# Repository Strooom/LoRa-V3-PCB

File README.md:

# LoRa-V3 PCB

KiCAD design files for the LoRa-V3-PCB.

## Renders
## Front

## Back

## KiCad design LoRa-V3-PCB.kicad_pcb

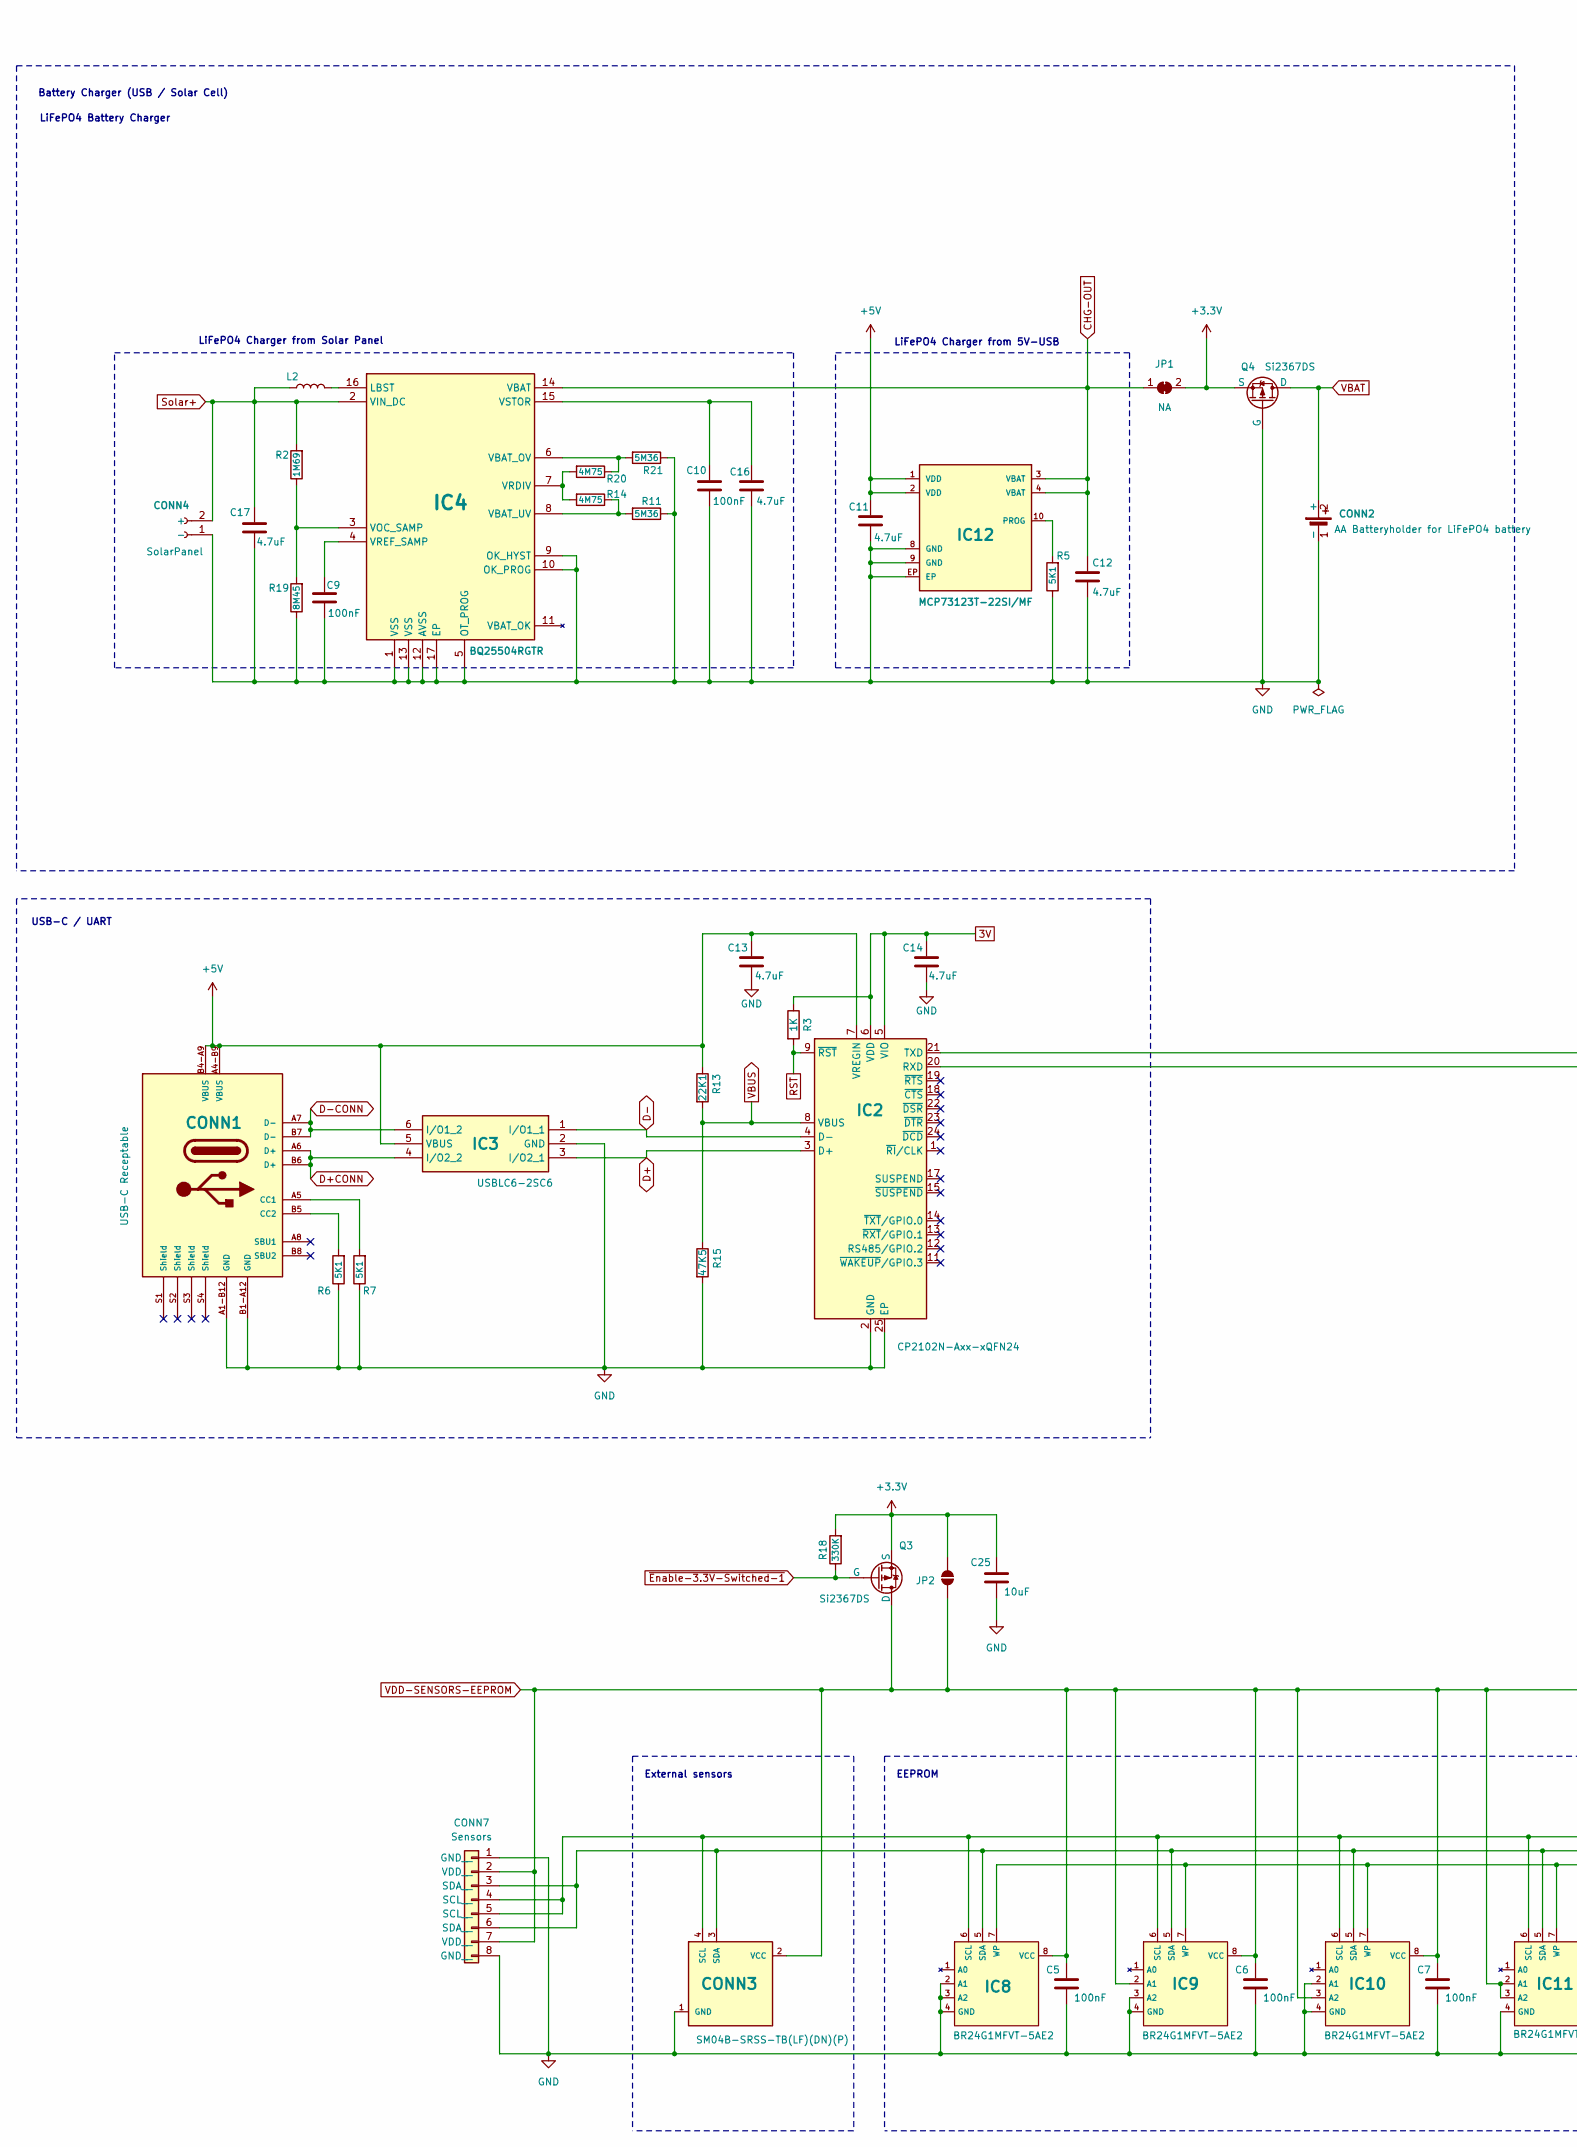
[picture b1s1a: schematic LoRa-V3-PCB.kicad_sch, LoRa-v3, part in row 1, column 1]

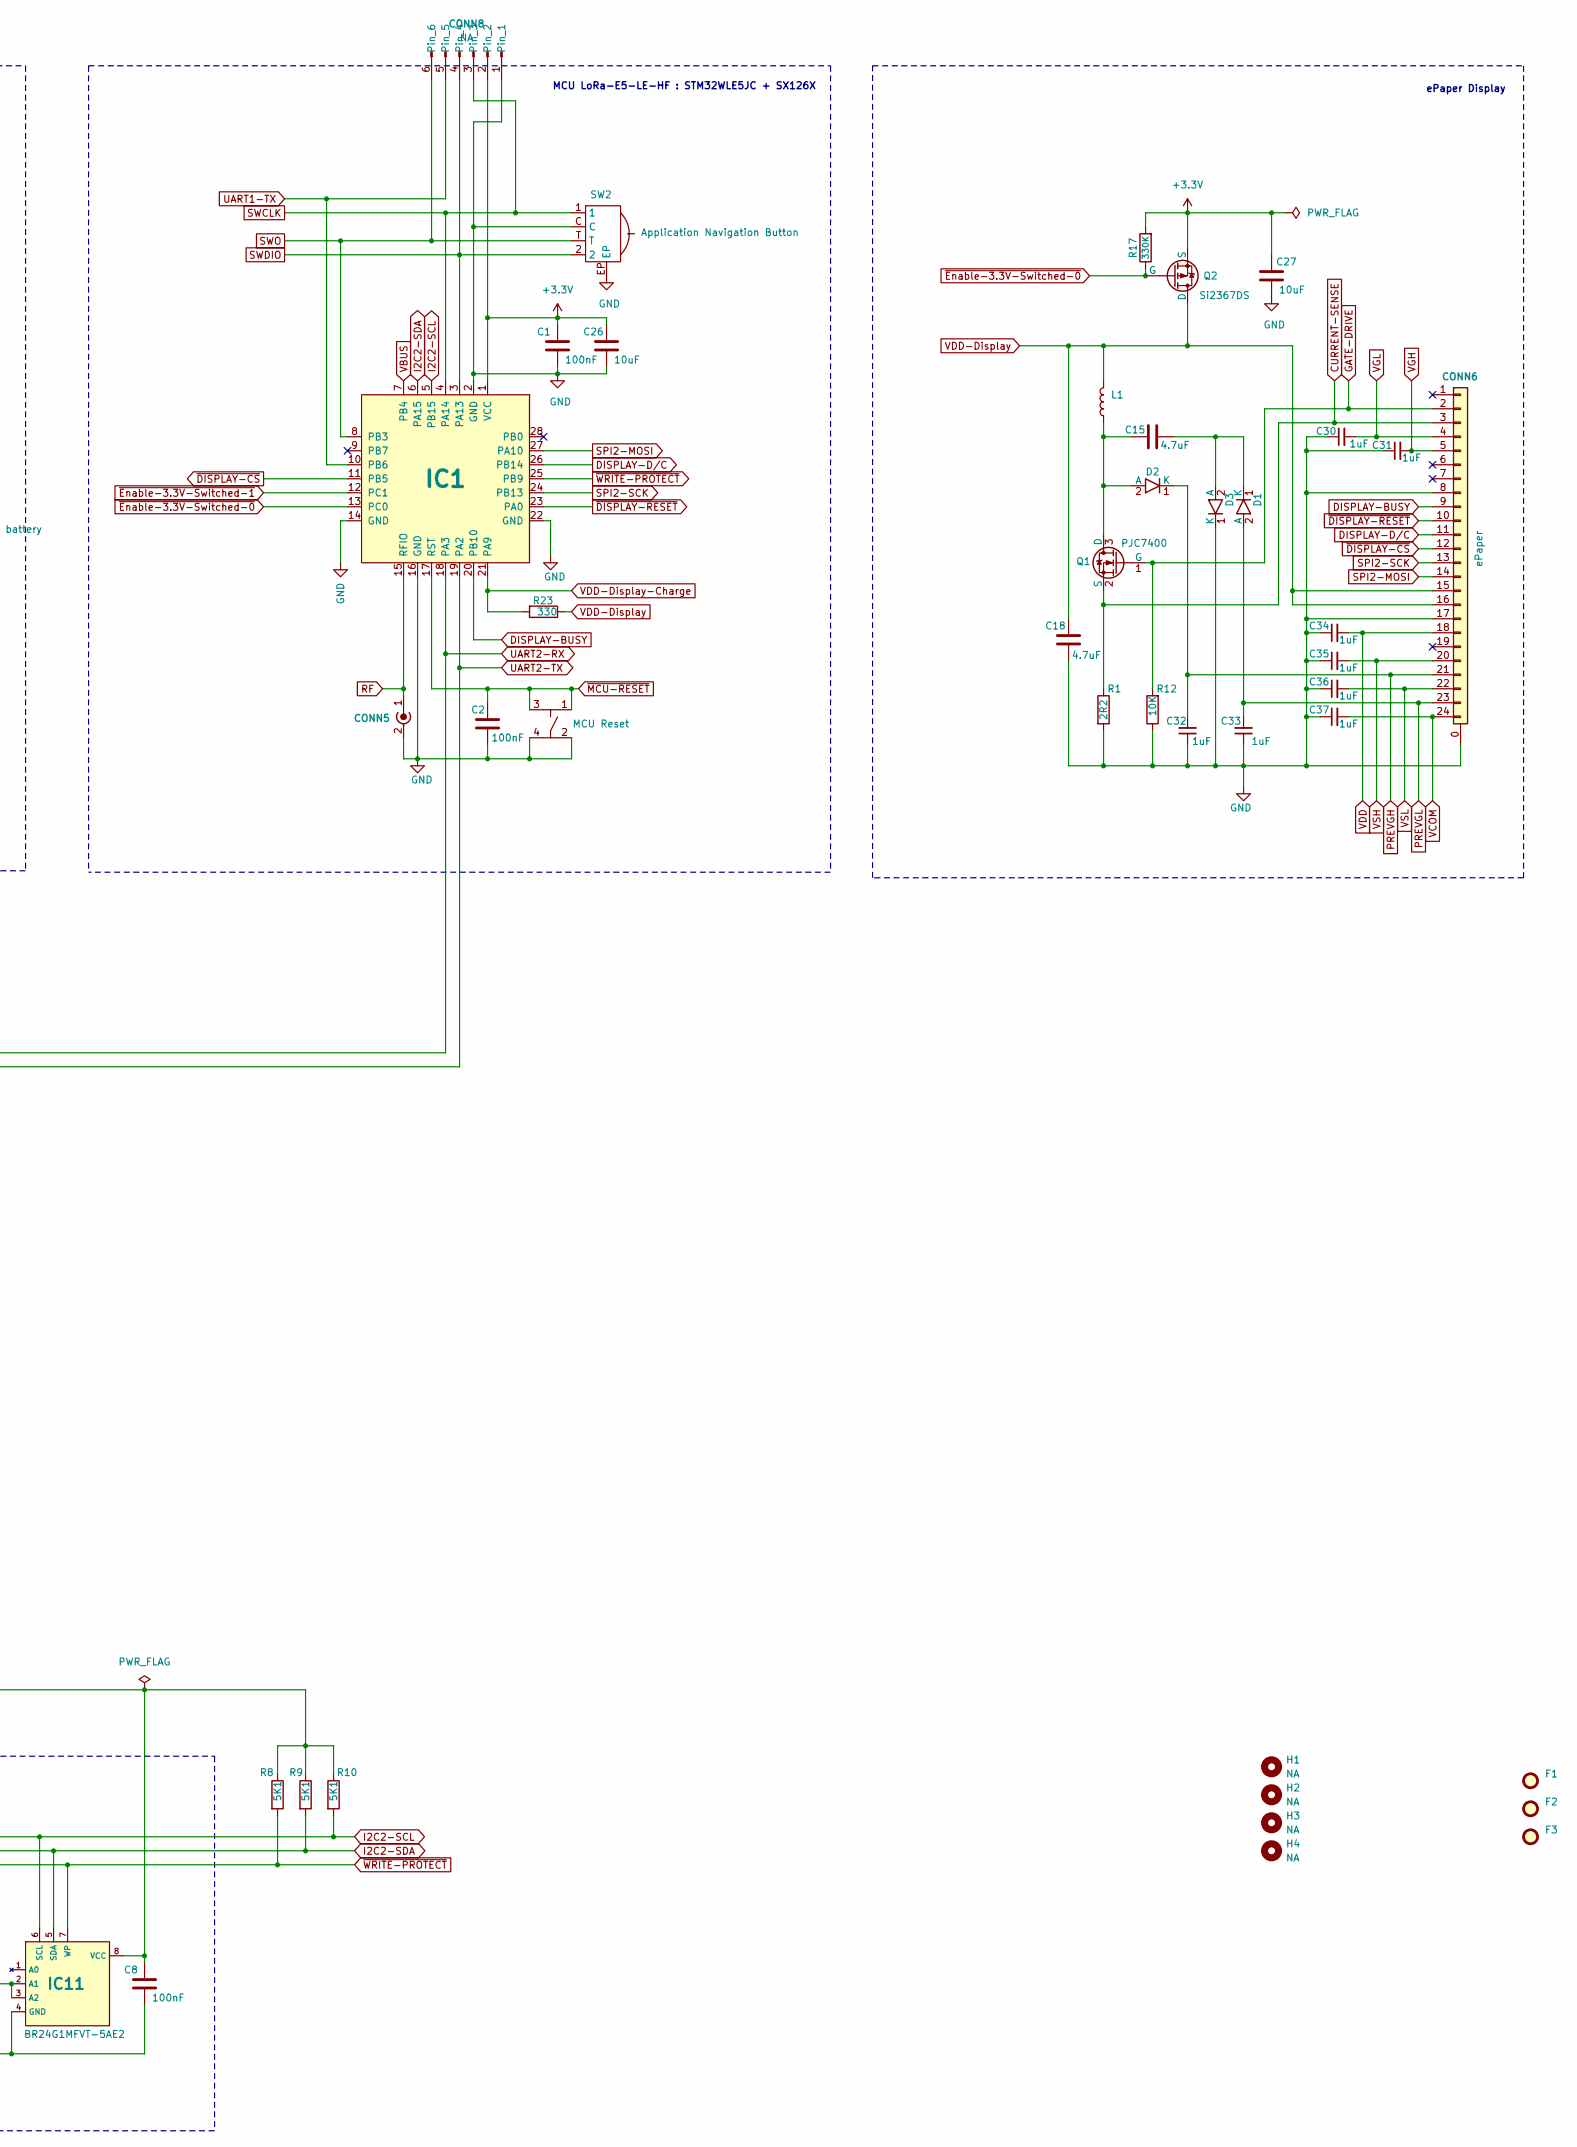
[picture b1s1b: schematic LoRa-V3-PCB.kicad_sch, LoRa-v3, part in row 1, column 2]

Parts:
C1, C2, C5, C6, C7, C8, C9, C10: 100nF; C_0603_nominal; manufacturerPartNumber CGA3E2X7R1E104K080AA
C11, C12, C13, C14, C15, C16, C17, C18: 4.7uF; C_0805; manufacturerPartNumber CL21B475KPFNFNE
C25, C26, C27: 10uF; C_0805; manufacturerPartNumber CL21B106KPQNNWE
C30, C31, C32, C33, C34, C35, C36, C37: 1uF; C_0603_nominal; manufacturerPartNumber CGA3E1X7R1E105K080AC
CONN1: 217179-0001; Molex-2171790001; manufacturerPartNumber 217179-0001
CONN2: AA Batteryholder for LiFePO4 battery; BAT_2460; manufacturerPartNumber 2460
CONN3: SM04B-SRSS-TB(LF)(DN)(P); JST_SH_SM04B-SRSS-TB_1x04-1MP_P1.00mm_Horizontal; manufacturerPartNumber SM04B-SRSS-TB(LF)(DN)(P)
CONN4: NA; PinHeader_1x02_P2.54mm_Vertical; manufacturerPartNumber B2B-XH-A(LF)(SN)
CONN5: 73391-0080; Molex 73391-0080; manufacturerPartNumber 73391-0080
CONN6: 2-1734839-4; TE_2-1734839-4_1x24-1MP_P0.5mm_Horizontal; manufacturerPartNumber 2-1734839-4
CONN7: Sensors; GCT_BC075-08-A-L-A; manufacturerPartNumber BC075-08-A-L-A
CONN8: NA; Debug_PinHeader_1x06_P2.00mm_Vertical; manufacturerPartNumber NA
D1, D2, D3: MSS1P3HM3_A/H; MSS1P3; manufacturerPartNumber MSS1P3HM3_A/H
F1, F2, F3: NA; Fiducial_0.5mm_Mask1mm; manufacturerPartNumber NA
H1, H2: NA; MountingHole_2mm_noCourtyard; manufacturerPartNumber NA
H3, H4: NA; MountingHole_2mm; manufacturerPartNumber NA
IC1: SeeedStudio Wio-E5-LE-HF; LoRa-E5; manufacturerPartNumber 114993121
IC2: CP2102N-Axx-xQFN24; QFN24-CP2102N; manufacturerPartNumber CP2102N-A02-GQFN24R
IC3: USBLC6-2SC6; SOT-23-6L-USBLC6-2; manufacturerPartNumber USBLC6-2SC6
IC4: BQ25504RGTR; VQFN-16-1EP_3x3mm_P0.5mm_EP1.6x1.6mm_ThermalVias; manufacturerPartNumber BQ25504RGTR
IC8, IC9, IC10, IC11: BR24G1MFVT-5AE2; BR24G1M-TSSOP-B8; manufacturerPartNumber BR24G1MFVT-5AE2
IC12: MCP73123T-22SI/MF; DFN10_MCP73123; manufacturerPartNumber MCP73123T-22SI/MF
JP1: NA; SolderJumper-2_P1.3mm_Bridged2Bar_Pad1.0x1.5mm; manufacturerPartNumber NA
JP2: NA; SolderJumper-2_P1.3mm_Open_TrianglePad1.0x1.5mm; manufacturerPartNumber NA
L1: 47uH; L_TDK_VLS3010CX; manufacturerPartNumber VLS3010CX-470M-1
L2: 22 uH; L_TDK_VLS3010CX; manufacturerPartNumber VLS3010CX-220M-1
Q1: PJC7400_R1_00001; SOT-323_PJC7400; manufacturerPartNumber PJC7400_R1_00001
Q2, Q3, Q4: Si2367DS; SI2367DS-SOT-23; manufacturerPartNumber SI2367DS-T1-GE3
R1: ERJ-3RQJ2R2V; R_0603_nominal; manufacturerPartNumber ERJ-3RQJ2R2V
R2: 1M69; R_0603_nominal; manufacturerPartNumber RC0603FR-071M69L
R3: 1K; R_0603_nominal; manufacturerPartNumber SR0603JR-071KL
R5, R6, R7, R8, R9, R10: 5K1; R_0603_nominal; manufacturerPartNumber AC0603DR-075K1L
R11, R21: 5M36; R_0603_nominal; manufacturerPartNumber CRCW06035M36FKEA
R12: 10K; R_0603_nominal; manufacturerPartNumber CR0603-JW-103ELF
R13: 22K1; R_0603_nominal; manufacturerPartNumber AC0603FR-0722K1L
R14, R20: 4M75; R_0603_nominal; manufacturerPartNumber RC0603FR-074M75L
R15: 47K5; R_0603_nominal; manufacturerPartNumber AC0603FR-0747K5L
R17, R18: 330K; R_0603_nominal; manufacturerPartNumber AC0603JR-07330KL
R19: 8M45; R_0603_nominal; manufacturerPartNumber RC0603FR-078M45L
R23: 330; R_0603_nominal; manufacturerPartNumber RC0603FR-7W330RL
SW1: 434331045822; Wurth-4343X10458XX; manufacturerPartNumber 434331045822
SW2: SLLB510100; manufacturerPartNumber SLLB510100

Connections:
3V: C14.1, IC2.5 (VIO), IC2.6 (VDD), R3.1
+3.3V: C1.1, C25.1, C26.1, C27.1, CONN8.2, IC1.1 (VCC), JP1.2 (B), JP2.2 (B), Q2.2 (S), Q3.2 (S), Q4.2 (S), R17.2, R18.2
+5V: C11.1, C13.1, CONN1.A4-B9 (VBUS), CONN1.B4-A9 (VBUS), IC2.7 (VREGIN), IC3.5 (VBUS), IC12.1 (VDD), IC12.2 (VDD), R13.1
CHG-OUT: C12.1, IC4.14 (VBAT), IC12.3 (VBAT), IC12.4 (VBAT), JP1.1 (A)
CURRENT-SENSE: CONN6.3, Q1.2 (S), R1.1
D+: IC2.3 (D+), IC3.3 (I/O2_1)
D+CONN: CONN1.A6 (D+), CONN1.B6 (D+), IC3.4 (I/O2_2)
D-: IC2.4 (D-), IC3.1 (I/O1_1)
D-CONN: CONN1.A7 (D-), CONN1.B7 (D-), IC3.6 (I/O1_2)
DISPLAY-BUSY: CONN6.9, IC1.20 (PB10)
DISPLAY-D/C: CONN6.11, IC1.26 (PB14)
GATE-DRIVE: CONN6.2, Q1.1 (G), R12.2
GND: C1.2, C2.2, C5.2, C6.2, C7.2, C8.2, C9.2, C10.2, C11.2, C12.2, C13.2, C14.2, C16.2, C17.2, C18.2, C25.2, C26.2, C27.2, C30.1, C31.1, C32.1, C33.1, C34.1, C35.1, C36.1, C37.1, CONN1.A1-B12 (GND), CONN1.B1-A12 (GND), CONN2.1 (-), CONN3.1 (GND), CONN4.1 (-), CONN5.2 (Ext), CONN6.0 (GND), CONN6.8, CONN6.17, CONN7.1 (GND__), CONN7.8 (GND__), CONN8.1, D3.1 (K), IC1.2 (GND), IC1.14 (GND), IC1.16 (GND), IC1.22 (GND), IC2.2 (GND), IC2.25 (EP), IC3.2 (GND), IC4.1 (VSS), IC4.5 (OT_PROG), IC4.9 (OK_HYST), IC4.10 (OK_PROG), IC4.12 (AVSS), IC4.13 (VSS), IC4.17 (EP), IC8.2 (A1), IC8.3 (A2), IC8.4 (GND), IC9.3 (A2), IC9.4 (GND), IC10.2 (A1), IC10.4 (GND), IC11.4 (GND), IC12.8 (GND), IC12.9 (GND), IC12.EP, Q4.1 (G), R1.2, R5.1, R6.1, R7.1, R11.1, R12.1, R15.2, R19.1, R21.1, SW1.2, SW1.4, SW2.C, SW2.EP
I2C2-SCL: CONN3.4 (SCL), CONN7.4 (SCL__), CONN7.5 (SCL__), IC1.5 (PB15), IC8.6 (SCL), IC9.6 (SCL), IC10.6 (SCL), IC11.6 (SCL), R10.2
I2C2-SDA: CONN3.3 (SDA), CONN7.3 (SDA__), CONN7.6 (SDA__), IC1.6 (PA15), IC8.5 (SDA), IC9.5 (SDA), IC10.5 (SDA), IC11.5 (SDA), R9.2
unnamed: CONN1.A5 (CC1), R7.2
unnamed: CONN1.B5 (CC2), R6.2
unnamed: C15.1, D1.1 (K), D3.2 (A)
unnamed: C15.2, D2.2 (A), L1.1, Q1.3 (D)
unnamed: IC4.16 (LBST), L2.2
unnamed: IC4.6 (VBAT_OV), R20.1, R21.2
unnamed: IC4.8 (VBAT_UV), R11.2, R14.1
unnamed: IC4.3 (VOC_SAMP), R2.1, R19.2
unnamed: IC4.7 (VRDIV), R14.2, R20.2
unnamed: C9.1, IC4.4 (VREF_SAMP)
unnamed: C10.1, C16.1, IC4.15 (VSTOR)
unnamed: IC12.10 (PROG), R5.2
PREVGH: C32.2, CONN6.21, D2.1 (K)
PREVGL: C33.2, CONN6.23, D1.2 (A)
RF: CONN5.1 (In), IC1.15 (RFIO)
RST: IC2.9 (~RST), R3.2
SPI2-MOSI: CONN6.14, IC1.27 (PA10)
SPI2-SCK: CONN6.13, IC1.24 (PB13~)
SWCLK: CONN8.3, IC1.4 (PA14), SW2.1
SWDIO: CONN8.4, IC1.3 (PA13), SW2.2
SWO: CONN8.6, IC1.8 (PB3), SW2.T
Solar+: C17.1, CONN4.2 (+), IC4.2 (VIN_DC), L2.1, R2.2
UART1-TX: CONN8.5, IC1.10 (PB6)
UART2-RX: IC1.18 (PA3), IC2.21 (TXD)
UART2-TX: IC1.19 (PA2), IC2.20 (RXD)
VBAT: CONN2.2 (+), Q4.3 (D)
VBUS: IC1.7 (PB4), IC2.8 (VBUS), R13.2, R15.1
VCOM: C37.2, CONN6.24
VDD: C34.2, CONN6.18
VDD-Display: C18.1, CONN6.15, CONN6.16, L1.2, Q2.3 (D), R23.1
VDD-Display-Charge: IC1.21 (PA9), R23.2
VDD-SENSORS-EEPROM: C5.1, C6.1, C7.1, C8.1, CONN3.2 (VCC), CONN7.2 (VDD__), CONN7.7 (VDD__), IC8.8 (VCC), IC9.2 (A1), IC9.8 (VCC), IC10.3 (A2), IC10.8 (VCC), IC11.2 (A1), IC11.3 (A2), IC11.8 (VCC), JP2.1 (A), Q3.3 (D), R8.1, R9.1, R10.1
VGH: C31.2, CONN6.5
VGL: C30.2, CONN6.4
VSH: C35.2, CONN6.20
VSL: C36.2, CONN6.22
~DISPLAY-CS: CONN6.12, IC1.11 (PB5)
~DISPLAY-RESET: CONN6.10, IC1.23 (PA0)
~Enable-3.3V-Switched-0: IC1.13 (PC0), Q2.1 (G), R17.1
~Enable-3.3V-Switched-1: IC1.12 (PC1), Q3.1 (G), R18.1
~MCU-RESET: C2.1, IC1.17 (RST), SW1.1, SW1.3
~WRITE-PROTECT: IC1.25 (PB9), IC8.7 (WP), IC9.7 (WP), IC10.7 (WP), IC11.7 (WP), R8.2

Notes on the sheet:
MCU LoRa-E5-LE-HF : STM32WLE5JC + SX126X
LiFePO4 Charger from 5V-USB
LiFePO4 Charger from Solar Panel
USB-C / UART
LiFePO4 Battery Charger
ePaper Display
EEPROM
Battery Charger (USB / Solar Cell)
External sensors

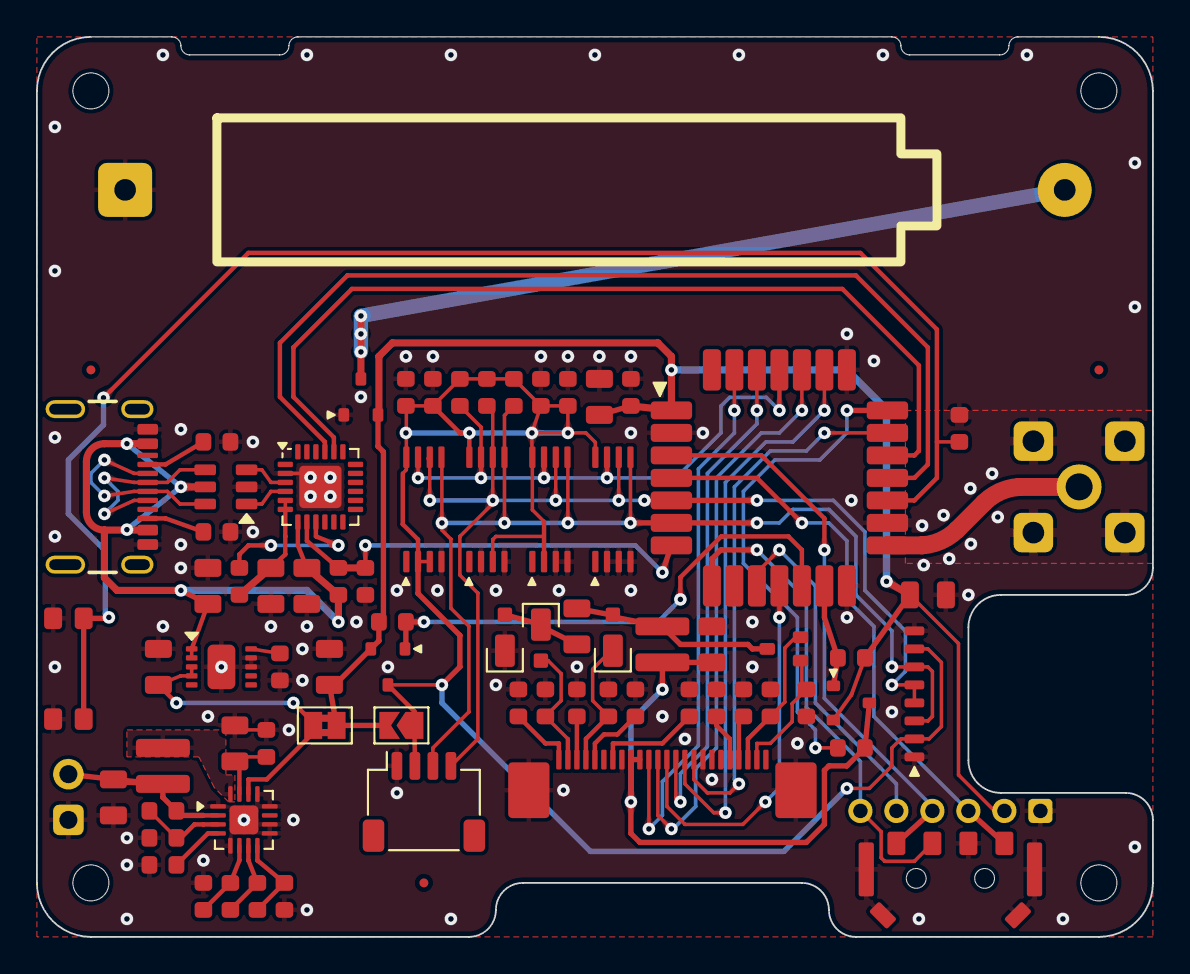
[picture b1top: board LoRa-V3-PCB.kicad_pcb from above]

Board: 2 copper layers, 62.0 x 50.0 mm, 85 parts (1 on the bottom side), 57 nets.

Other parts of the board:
G01: CC-LOGO; CreativeCommonsLogo

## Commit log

2024-09-23 Add schematic in pdf format
2024-10-10 Add wrokflow
2024-10-10 fix DRC error
2024-10-10 add workflow generated files
2024-10-10 add readme
2024-10-10 fix readme
2024-10-18 fix ERC warnings
2025-02-06 upgrade repo to new workflow
    expecting errors...
2025-02-06 bom fixes
2025-02-06 bom cleanup
2025-02-06 fix bom
    removing extra fields
2025-02-06 fix footprints
2025-02-06 removed back render from kibot
2025-02-06 outcommented blender render
2025-02-06 testing render output
2025-02-06 render test
2025-02-06 improved camera
2025-02-06 adjust resolution
2025-02-06 lighting
2025-02-06 tuning light
2025-02-06 more energy to light
2025-02-06 fix lights
2025-02-06 export model
2025-02-06 experiments
2025-02-06 fix distance to PCB
2025-02-06 small
2025-02-06 several fixes
2025-02-06 fix SHT40 footprint
2025-02-18 finish solar power harvester
2025-02-20 improve solar layout
2025-02-24 reworked for 0805 capacitors
2025-02-24 fix missing 3D models
2025-02-24 fix footprint for CP2102N
2025-02-24 add permanent vdd for sensors with solder bridge
2025-02-24 re-enable full workflow
2025-02-24 fix missing datasheet on JP2
2025-02-24 fix JP2 metadata
2025-02-24 add extra csv file for kicost
2025-02-24 remove connectors from BOM
2025-02-24 exclude api keys from tracking
2025-03-11 add silkscreen logo version and date
2025-03-11 fix BOM
2025-03-11 fix BOM 2
2025-03-11 major Major release v1.0
2025-03-11 testing rendering
2025-03-12 fix render outputs
2025-03-19 replace 5M36 resistor
    by a variant which is in stock
2025-03-19 fix metadata on L1
2025-03-19 update on USB ESD protection - partnumber
2025-03-19 cleanup bom on IC3
2025-04-16 final version with sensors on PCB
2025-04-17 routing complete
2025-04-17 cleaner routing
2025-04-23 small routing improvements
2025-04-23 repo cleanup
2025-04-23 repo cleanup
    add license
    add back render
2025-07-02 correct pins on sensor connector
    SDA and SCL were reversed
2025-08-07 layout improvements
    put solder bridges on front layer
    more gnd connectivity
2025-08-07 replace battery holder
    to Keystone 2460
2025-08-07 improve battery holder footprint
2025-08-08 move SMA connector
    to board edge so more thread is available outside the enclosure
2025-09-04 extend KiBOT with export of Gerbers
2025-09-04 fix gerber export with kibot
2025-09-04 fix kibot gerbers export
2025-09-04 testing gerber export
2025-09-04 add drill export to kibot
2025-10-15 upgrade workflow
2025-10-21 license updates
2025-10-21 add gerber output to workflow
2025-10-21 improved .gitignore
2025-10-27 layout improvements per review report

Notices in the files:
README.md:
License: MIT
